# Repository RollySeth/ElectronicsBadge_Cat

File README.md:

# ElectronicsBadge_Cat
To make a LED badge with basic through-hole components 

## Parts List-

1. 3mm LEDs (Two)
2. 100 Ohms Resistor (One)
3. CR2032 3V coin cell battery (One)
4. SPDT Slide Switch - EG1218 (DigiKey - EG1903-ND) (One)
5. CR2032 Battery Holder PC PIN (DigiKey- BAT-HLD-001-THM-ND) (One)
6. [Clutch Tie-Tack Pin Back](https://www.amazon.com/gp/product/B0759PMB12/ref=oh_aui_search_detailpage?ie=UTF8&psc=1) (pin size - 4.5 mm in diameter) (One)

Steps-

Step1-
Make sure you have all thre required parts-

& all the related equipment-

Step 2-
Start with Soldering the resistor. 
Ben resistor ends and slide them through the pcb hole. The resistors dont have direction so you can place it in any orientation. Add flux to the pcb holes before soldering

Step 3-
Solder the LEDs - make sure the terminals are placed as shown in the image below- 

Step 4-
Next, add CR2032 battery holder

Step 5- 
Now solder SPDT Switch

Step 6-
Finally, solder the clutch pin back

Step 7- 
Slide-in CR2032  battery & test the pcb

Remove the extra flux from the pcb using a q-tip and alcohol

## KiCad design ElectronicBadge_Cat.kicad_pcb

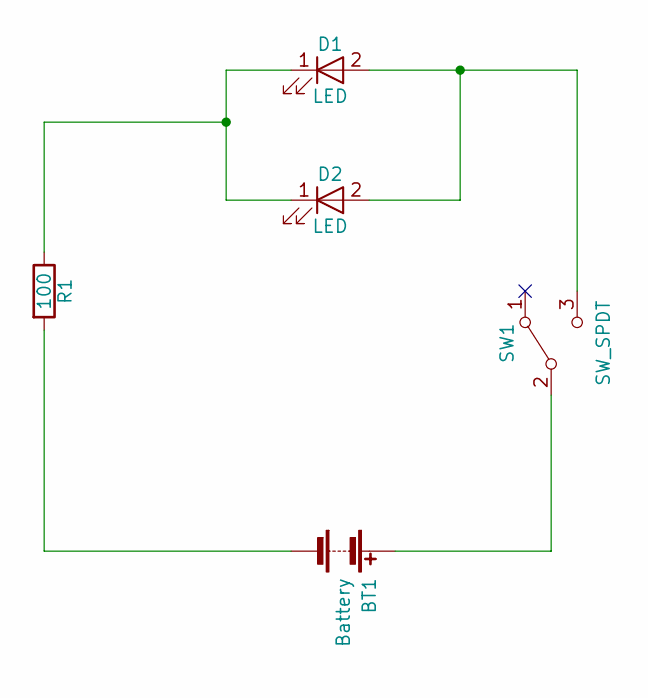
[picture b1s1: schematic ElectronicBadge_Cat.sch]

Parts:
BT1: Battery; BATT_CR2032
D1, D2: LED; LED_D3.0mm
R1: 100; R_Axial_DIN0207_L6.3mm_D2.5mm_P10.16mm_Horizontal
SW1: SW_SPDT; SW_Micro_SPST

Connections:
unnamed: BT1.1 (+), SW1.2 (B)
unnamed: BT1.2 (-), R1.2
unnamed: D1.1 (K), D2.1 (K), R1.1
unnamed: D1.2 (A), D2.2 (A), SW1.3 (C)

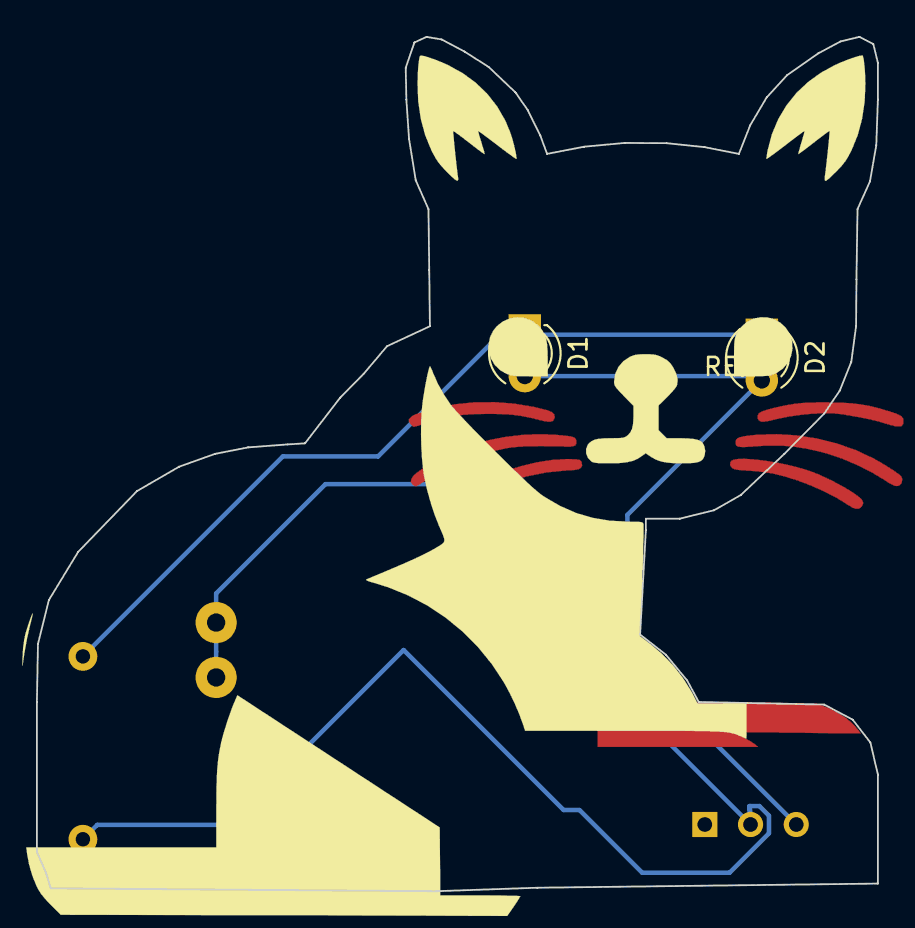
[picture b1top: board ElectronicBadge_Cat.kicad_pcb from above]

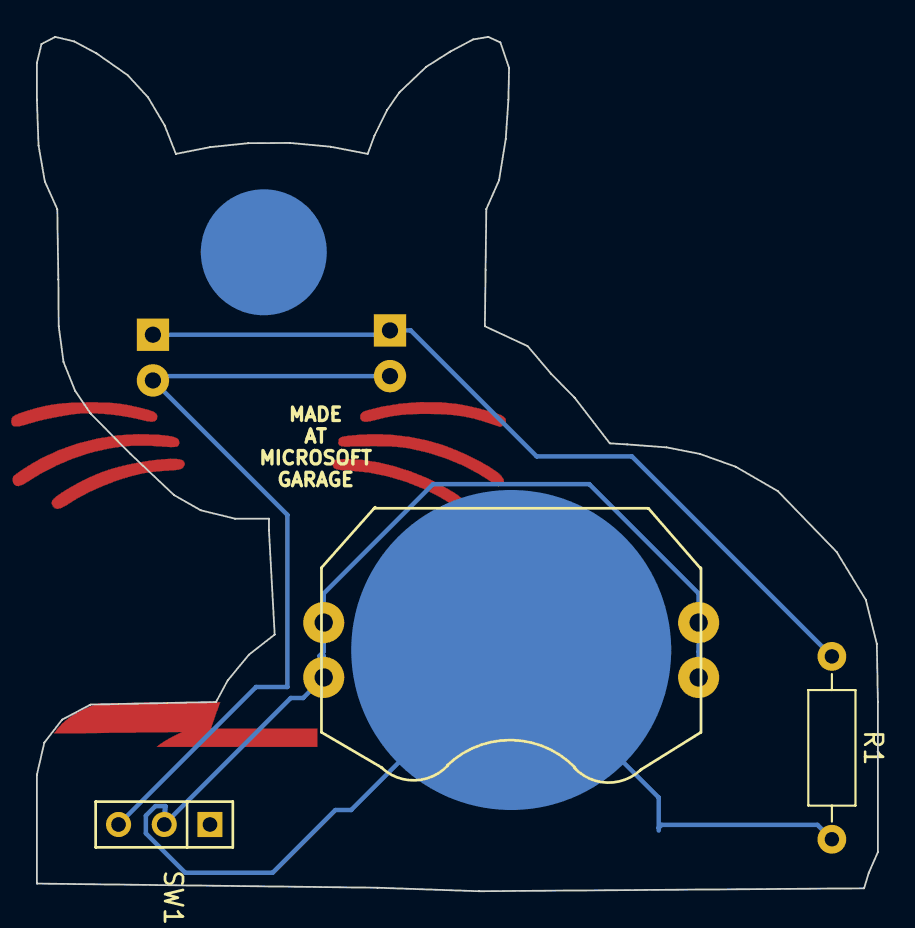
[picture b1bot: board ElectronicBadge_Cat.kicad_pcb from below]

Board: 2 copper layers, 46.7 x 47.5 mm, 5 parts (3 on the bottom side), 4 nets.

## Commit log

2018-09-30 Images Folder Added
2018-09-30 Adding ReadMe image
2018-10-03 Added KiCAD files
2018-10-03 Added Parts List
2018-10-08 ReadMe updated- images
2018-10-08 Updates ReadMe- steps
